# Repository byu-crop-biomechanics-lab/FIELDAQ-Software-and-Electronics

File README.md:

# FIELDAQ

## Running the Software on Raspberry PI 
1. Download the SD card [image](https://byu.box.com/s/8bjvmoukdaxu5hu80yromtlmhrw2ap65). You need at least a 16 GB SD card. 
2. Flash the SD card with the new image using whatever flash software you are accustomed to. For mac users I'd recommend using Apple PI Baker. 
3. Once flashed the device will open automatically in the command line interface and will boot the program automatically. Don't forget to to go to the settings and click the "update with github", or do it manually through the command line. 
4. If you want to make edits to the software or system as a whole and want to have a GUI, you can run the startx command and it will switch over to the Linux GUI. 

## Running the Software on Linux System (Non-Raspberry PI)
Run the following commands in a bash terminal to download, build and run the projcet. This build script will build a python environment and download the necessary packages. It then will build the project and run it to verify that everything is working correctly. 
```
git clone git@github.com:byu-crop-biomechanics-lab/FIELDAQ-Software-and-Electronics.git
cd FIELDAQ-Software-and-Electronics/
source build_project
```

After installing python and the nessesary [libraries](https://github.com/byu-crop-biomechanics-lab/FIELDAQ-Software-and-Electronics/blob/master/libraries.txt), the software is run by navigating into the [Granusoft/src](https://github.com/pr1ce1227/REAPER/tree/main/Granusoft/src) directory and running the [main.py](https://github.com/byu-crop-biomechanics-lab/FIELDAQ-Software-and-Electronics/blob/master/Granusoft/src/main.py) file.

The [main.py](https://github.com/byu-crop-biomechanics-lab/FIELDAQ/blob/master/Granusoft/src/main.py) file imports the necessary kivy library elements, and builds the kivy app. The companion [main.kv](https://github.com/byu-crop-biomechanics-lab/FIELDAQ-Software-and-Electronics/blob/master/Granusoft/src/main.kv) file imports the widgets (GUI screen elements), created for the use across the GUI, and imports the views that will be displayed throughout the app. These views are each composed of a python file and kivy file. More detail can be found in [Documentation/Kivy Screen Management.docx](https://github.com/byu-crop-biomechanics-lab/FIELDAQ-Software-and-Electronics/blob/master/Documentation/Kivy%20Screen%20Management.docx).

## Overview and Resources
The software for the FIELDAQ is written in python, using the kivy library. Versioning is managed using git via GitHub. The layout and functionality are based on the old DARLING software. With the addition of a touchscreen, kivy was utilized over pygame.

- [Resources for Python](https://www.python.org/about/gettingstarted/)
- Resources for kivy can be found in [Documentation/Kivy Training Resources](https://github.com/byu-crop-biomechanics-lab/FIELDAQ-Software-and-Electronics/tree/master/Documentation/Kivy%20Training%20Resources.docx)
- [Resources for git](https://guides.github.com/introduction/git-handbook/)
  - [The old DARLING repository](https://github.com/byu-crop-biomechanics-lab/DARLING_Software.git)

## Documentation Directory
The Documentation directory contains many useful files, some of which have been mentioned previously. Documentation that has been found to be the most useful is listed here:
- [Setup Software for Non-RPi Computers.txt](https://github.com/byu-crop-biomechanics-lab/FIELDAQ-Software-and-Electronics/blob/master/Documentation/Setup%20Software%20for%20Non-RPi%20Computers.txt) -  Information on how to get the GUI running on a non-RaspberryPi computer for software development.
- [Software Update Procedure.md](https://github.com/byu-crop-biomechanics-lab/FIELDAQ-Software-and-Electronics/blob/master/Documentation/Software%20Update%20Procedure.md) - Information on how to utilize a USB drive or Github when updating the on-device software.
- [FIELDAQ_Software_Diagrams.pdf](https://github.com/byu-crop-biomechanics-lab/FIELDAQ-Software-and-Electronics/blob/master/Documentation/FIELDAQ_Software_Diagrams.pdf) - Information about the screen navigation for the GUI and how each screen is built using kivy elements/widgets (flowchart is outdated).
- [Example_Adding the Camera Module.docx](https://github.com/byu-crop-biomechanics-lab/FIELDAQ-Software-and-Electronics/blob/master/Documentation/Example_Adding%20the%20Camera%20Module.docx) - A reflection on how the camera screens were added.
- [Example_Adding a Boot Screen.docx](https://github.com/byu-crop-biomechanics-lab/FIELDAQ-Software-and-Electronics/blob/master/Documentation/Example_Adding%20a%20Boot%20Screen.docx) - A hypothetical situation where a boot screen is created to choose between the Camera test mode and the Stalk Push testing mode.

### Structural Information of the Code Base (how is it assembled)
- [Directory Tree.txt](https://github.com/byu-crop-biomechanics-lab/FIELDAQ-Software-and-Electronics/blob/master/Documentation/Directory%20Tree.txt) -  Overview of the directories in the repository. With information about the contents of each directory.
- [FIELDAQ_Software_Diagrams.pdf](https://github.com/byu-crop-biomechanics-lab/FIELDAQ-Software-and-Electronics/blob/master/Documentation/FIELDAQ_Software_Diagrams.pdf) - 	Information about the screen navigation for the GUI and how each screen is built using kivy elements/widgets (flowchart is outdated).
- [Software Flowchart and Logic.docx](https://github.com/byu-crop-biomechanics-lab/FIELDAQ-Software-and-Electronics/blob/master/Documentation/Software%20Flowchart%20and%20Logic.docx) - 	Supplementary to FIELDAQ_Software_Diagrams, this document contains more information about the purpose of each screen.
- [Software Documentation Outdated.pdf](https://github.com/byu-crop-biomechanics-lab/FIELDAQ-Software-and-Electronics/blob/master/Documentation/Software%20Documentation%20Outdated.pdf) - 	An old resource containing the Classes and Methods contained in every file. This was last updated at the end of capstone, and may contain some useful information still. An updated version can be compiled using [DoxyGen](https://www.doxygen.nl/index.html) (version. 1.8.15).
### Background Information (how do the pieces work)
- [Kivy Screen Management.docx](https://github.com/byu-crop-biomechanics-lab/FIELDAQ-Software-and-Electronics/blob/master/Documentation/Kivy%20Screen%20Management.docx) - 	Information on how kivy navigates between screens and how screens can be added to the GUI.
- [Kivy Training Resources.docx](https://github.com/byu-crop-biomechanics-lab/FIELDAQ-Software-and-Electronics/blob/master/Documentation/Kivy%20Training%20Resources.docx) - 	A list of resources on how to learn kivy for those who are unfamiliar with the libraries.
- [Setup Software for Non-RPi Computers.txt](https://github.com/byu-crop-biomechanics-lab/FIELDAQ-Software-and-Electronics/blob/master/Documentation/Setup%20Software%20for%20Non-RPi%20Computers.txt) -  Information on how to get the GUI running on a non-RaspberryPi computer for software development.
- [Software Coding Standard.docx](https://github.com/byu-crop-biomechanics-lab/FIELDAQ-Software-and-Electronics/blob/master/Documentation/Software%20Coding%20Standard.docx) -	The Coding Standard for coding used throughout the software.
- [Software Update Procedure.md](https://github.com/byu-crop-biomechanics-lab/FIELDAQ-Software-and-Electronics/blob/master/Documentation/Software%20Update%20Procedure.md) - 	Information on how to utilize GitHub when updating the on-device software.
- Supplementary Directory:
  - [Kivy Clock Summary.docx](https://github.com/byu-crop-biomechanics-lab/FIELDAQ-Software-and-Electronics/blob/master/Documentation/Supplementary/Kivy%20Clock%20Summary.docx) - 	Information recorded by the capstone team about the logic for using the clock the way they did.
  - [Raspberry Pi Setup.docx](https://github.com/byu-crop-biomechanics-lab/FIELDAQ-Software-and-Electronics/blob/master/Documentation/Supplementary/Raspberry%20Pi%20Setup.docx) - 	Information on how to set up a new raspberry pi from scratch to host the software.
### Examples
- [Example_Adding the Camera Module.docx](https://github.com/byu-crop-biomechanics-lab/FIELDAQ-Software-and-Electronics/blob/master/Documentation/Example_Adding%20the%20Camera%20Module.docx) - A reflection on how the camera screens were added.
- [Example_Adding a Boot Screen.docx](https://github.com/byu-crop-biomechanics-lab/FIELDAQ-Software-and-Electronics/blob/master/Documentation/Example_Adding%20a%20Boot%20Screen.docx) - A hypothetical situation where a boot screen is created to choose between the Camera test mode and the Stalk Push testing mode.

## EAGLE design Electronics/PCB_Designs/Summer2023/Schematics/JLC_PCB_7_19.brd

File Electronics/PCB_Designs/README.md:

# PCB

The PCB_Designs sections gives current PCB files as well as files to help with the DRC, Gerber and BOM/CPL Files 
- Used www.jlcpcb.com for production

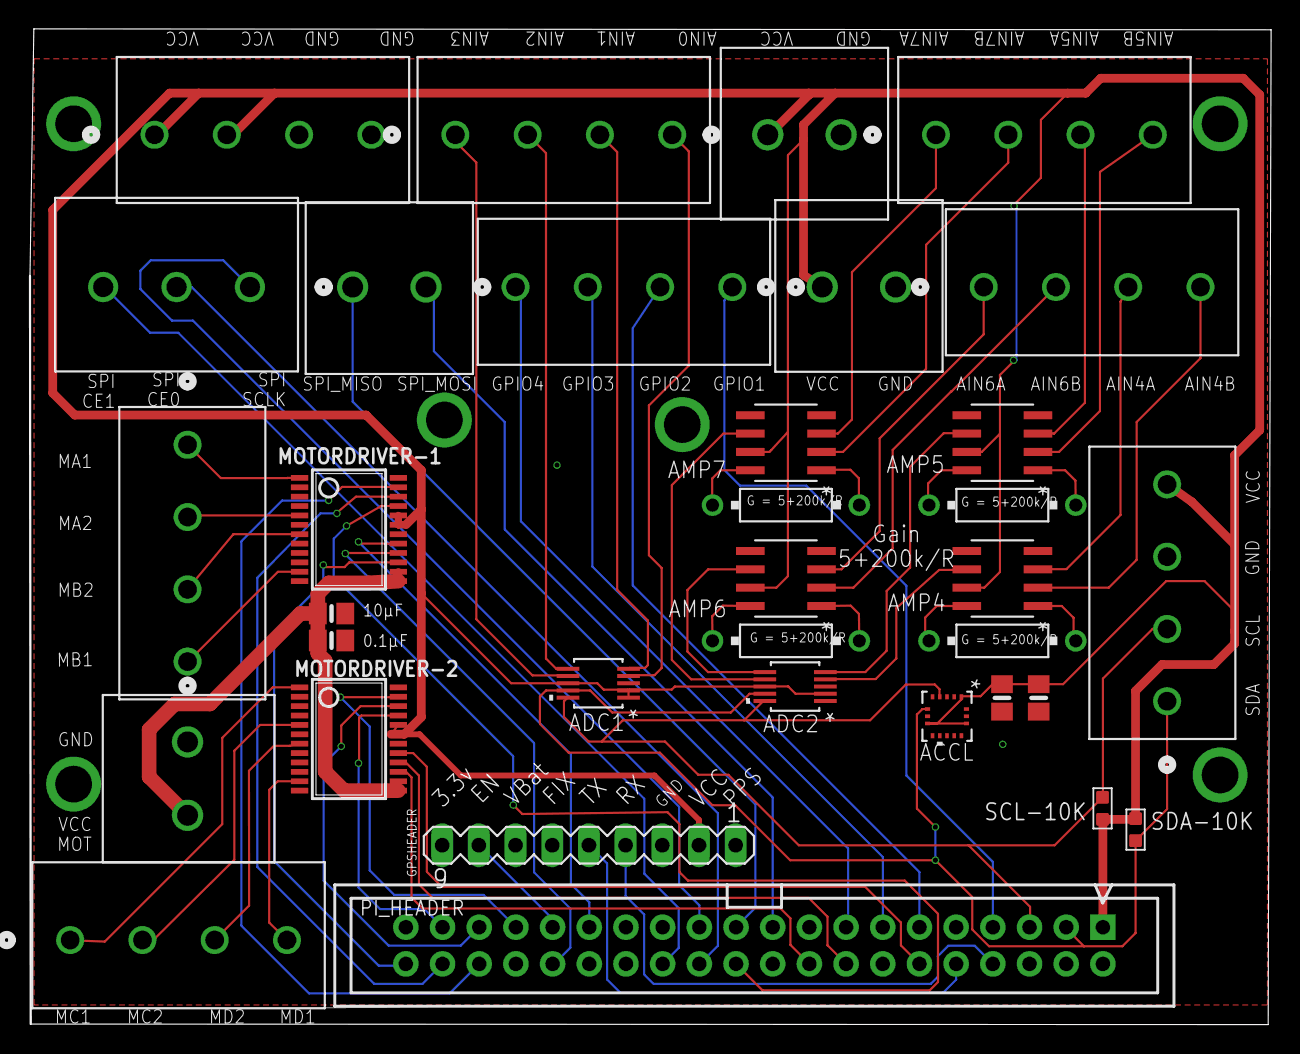
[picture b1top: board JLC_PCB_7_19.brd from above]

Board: 2 copper layers, 85.9 x 68.8 mm, 34 parts (0 on the bottom side), 61 nets.

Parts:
ACCL: LIS3DHTR; LGA-16_3X3X1MM
ADC1, ADC2: ADS1115IDGSR; DGS10
ADC2_AIN4_AMP, ADC2_AIN5_AMP, ADC2_AIN6_AMP, ADC2_AIN7_AMP: AD627ARZ-R7; R_8_ADI
ADC_1A_PWR, ADC_1A_SIG, ADC_2A_SIG, ADC_2B_SIG: 1715048; CONN_1715048_PXC
ADC_2A_PWR, ADC_2B_PWR: 1730612; CONN02_1730612_11P34X11P62_PXC
GPIO_A_: 1715048; CONN_1715048_PXC
GPIO_SPIA1: 1730612; CONN02_1730612_11P34X11P62_PXC
GPIO_SPIA2: 1730405; CONN_1730405_PXC
GPSHEADER: MA09-1
I2CA_: 1715048; CONN_1715048_PXC
MOTORDRIVER-1, MOTORDRIVER-2: TB6612 SSOP; SSOP24
MOTOR_1_A, MOTOR_2_: 1715048; CONN_1715048_PXC
MOTOR_1_B: 1730612; CONN02_1730612_11P34X11P62_PXC
PI_HEADER: RASPI_GPIO_B+#_BOX; RASPI_GPIO_B+_BOX
R5, R6, R7, R8: HPS58
SCL-10K: 10K 1/10W; R0603
SDA-10K: 10K 1/10W; R0603
VCC_10UF: 10µF; 0805-NO
VCC_.1UF: 0.1µF; 0805-NO
VMOTOR_10UF: 10µF; 0805-NO
VMOTOR_.1UF: 0.1µF; 0805-NO

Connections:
ADC1_AIN0: ADC1.4, ADC_1A_SIG.4
ADC1_AIN1: ADC1.5, ADC_1A_SIG.3
ADC1_AIN2: ADC1.6, ADC_1A_SIG.2
ADC1_AIN3: ADC1.7, ADC_1A_SIG.1
ADC2_AIN4: ADC2.4, ADC2_AIN4_AMP.6
ADC2_AIN4A: ADC2_AIN4_AMP.3, ADC_2B_SIG.3
ADC2_AIN4B: ADC2_AIN4_AMP.2, ADC_2B_SIG.4
ADC2_AIN5: ADC2.5, ADC2_AIN5_AMP.6
ADC2_AIN5A: ADC2_AIN5_AMP.3, ADC_2A_SIG.3
ADC2_AIN5B: ADC2_AIN5_AMP.2, ADC_2A_SIG.4
ADC2_AIN6: ADC2.6, ADC2_AIN6_AMP.6
ADC2_AIN6A: ADC2_AIN6_AMP.3, ADC_2B_SIG.1
ADC2_AIN6B: ADC2_AIN6_AMP.2, ADC_2B_SIG.2
ADC2_AIN7: ADC2.7, ADC2_AIN7_AMP.6
ADC2_AIN7A: ADC2_AIN7_AMP.3, ADC_2A_SIG.1
ADC2_AIN7B: ADC2_AIN7_AMP.2, ADC_2A_SIG.2
ADC_1: GPIO_SPIA1.1, PI_HEADER.19
AIN1: MOTORDRIVER-1.21, PI_HEADER.22
AIN2: MOTORDRIVER-1.22, PI_HEADER.38
BIN1: MOTORDRIVER-1.17, PI_HEADER.29
BIN2: MOTORDRIVER-1.16, PI_HEADER.32
CIN1: MOTORDRIVER-2.21, PI_HEADER.37
CIN2: MOTORDRIVER-2.22, PI_HEADER.35
DIN1: MOTORDRIVER-2.17, PI_HEADER.12
DIN2: MOTORDRIVER-2.16, PI_HEADER.16
EN: GPSHEADER.8, PI_HEADER.31
GND: ACCL.5, ACCL.7, ACCL.10, ACCL.12, ACCL.13, ACCL.15, ACCL.16, ADC1.3, ADC2.1, ADC2.3, ADC2_AIN4_AMP.4, ADC2_AIN4_AMP.5, ADC2_AIN5_AMP.4, ADC2_AIN5_AMP.5, ADC2_AIN6_AMP.4, ADC2_AIN6_AMP.5, ADC2_AIN7_AMP.4, ADC2_AIN7_AMP.5, ADC_1A_PWR.3, ADC_1A_PWR.4, ADC_2A_PWR.2, ADC_2B_PWR.2, GPSHEADER.3, I2CA_.3, MOTORDRIVER-1.3, MOTORDRIVER-1.4, MOTORDRIVER-1.9, MOTORDRIVER-1.10, MOTORDRIVER-1.18, MOTORDRIVER-2.3, MOTORDRIVER-2.4, MOTORDRIVER-2.9, MOTORDRIVER-2.10, MOTORDRIVER-2.18, MOTOR_1_B.1, PI_HEADER.6, PI_HEADER.9, PI_HEADER.14, PI_HEADER.20, PI_HEADER.25, PI_HEADER.30, PI_HEADER.34, PI_HEADER.39, VCC_10UF.2, VCC_.1UF.2, VMOTOR_10UF.2, VMOTOR_.1UF.2
GPIO1: GPIO_A_.1, PI_HEADER.7
GPIO2: GPIO_A_.2, PI_HEADER.11
GPIO3: GPIO_A_.3, PI_HEADER.13
GPIO4: GPIO_A_.4, PI_HEADER.15
MA1: MOTORDRIVER-1.1, MOTOR_1_A.1
MA2: MOTORDRIVER-1.5, MOTOR_1_A.2
MB1: MOTORDRIVER-1.11, MOTOR_1_A.4
MB2: MOTORDRIVER-1.7, MOTOR_1_A.3
MC1: MOTORDRIVER-2.1, MOTOR_2_.1
MC2: MOTORDRIVER-2.5, MOTOR_2_.2
MD1: MOTORDRIVER-2.11, MOTOR_2_.4
MD2: MOTORDRIVER-2.7, MOTOR_2_.3
unnamed: ADC2_AIN6_AMP.1, R5.1
unnamed: ADC2_AIN6_AMP.8, R5.2
unnamed: ADC2_AIN4_AMP.1, R7.1
unnamed: ADC2_AIN4_AMP.8, R7.2
unnamed: ADC2_AIN5_AMP.1, R8.1
unnamed: ADC2_AIN5_AMP.8, R8.2
unnamed: ADC2_AIN7_AMP.1, R6.1
unnamed: ADC2_AIN7_AMP.8, R6.2
PWMA: MOTORDRIVER-1.23, PI_HEADER.36
PWMB: MOTORDRIVER-1.15, PI_HEADER.40
PWMC: MOTORDRIVER-2.23, PI_HEADER.33
PWMD: MOTORDRIVER-2.15, PI_HEADER.18
RX: GPSHEADER.4, PI_HEADER.8
SCL: ACCL.4, ADC1.10, ADC2.10, I2CA_.2, PI_HEADER.5, SCL-10K.1
SDA: ACCL.6, ADC1.9, ADC2.9, I2CA_.1, PI_HEADER.3, SDA-10K.1
SPI_CE0: GPIO_SPIA2.2, PI_HEADER.24
SPI_CE1: GPIO_SPIA2.3, PI_HEADER.26
SPI_MISO: GPIO_SPIA1.2, PI_HEADER.21
SPI_SCLK: GPIO_SPIA2.1, PI_HEADER.23
TX: GPSHEADER.5, PI_HEADER.10
VCC: ACCL.1, ACCL.8, ACCL.14, ADC1.1, ADC1.2, ADC1.8, ADC2.2, ADC2.8, ADC2_AIN4_AMP.7, ADC2_AIN5_AMP.7, ADC2_AIN6_AMP.7, ADC2_AIN7_AMP.7, ADC_1A_PWR.1, ADC_1A_PWR.2, ADC_2A_PWR.1, ADC_2B_PWR.1, GPSHEADER.2, I2CA_.4, MOTORDRIVER-1.19, MOTORDRIVER-1.20, MOTORDRIVER-2.19, MOTORDRIVER-2.20, PI_HEADER.1, SCL-10K.2, SDA-10K.2, VCC_10UF.1, VCC_.1UF.1
VMOTOR: MOTORDRIVER-1.13, MOTORDRIVER-1.14, MOTORDRIVER-2.13, MOTORDRIVER-2.14, MOTOR_1_B.2, VMOTOR_10UF.1, VMOTOR_.1UF.1

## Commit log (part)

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2019-06-10 changed a file name to not have spaces
2019-06-10 Adjusted graphs on TestingResults and TestInProgress to automatically scale y axis to data in increments of 250.
2019-06-11 Adjusted y-scaling to improve calculation efficiency on device. Made graph backgrounds higher contrast.
2019-06-11 Re-added y-scaling after determining it is likely plotting all of the points on 2 graphs that could be causing time delays. Adjusted plot feature to plot only every 5th data point
2019-06-11 fixed .gitignore to ignore pycache files
2019-06-11 Added .gitignore file and deleted all pycaches.
2019-06-12 adjusted .gitignore file to address on device issues with .json files
2019-06-12 Adjusted config.json git settings to make configuration independant from software.
2019-06-12 adjusted how config was handled by git
2019-06-12 Adjusted Temperature sensor feed on main screen
2019-06-12 Fixed issue with trigger event for updating feed on the device
2019-06-13 Fixed update button
2019-06-13 Address error where no real data could cause a crash
2019-06-13 Added software update screen to move to when software update button is pressed.
2019-06-13 Adjusted testingresultsscreen
2019-06-13 Adding to previous commit, forgot to stage this change
2019-06-13 Adjusted how many digits are displayed on mainscreen and livefeedscreen. Adjusted layout of livefeedscreen to fit full coordinates.
2019-06-15 Undid unintentional change to elements.kv
2019-06-17 Added support to export location, temperature and humidity data in tests. Previously a pre-determined 40 value was given
2019-06-17 Fixed issue of mismatched parantheses
2019-06-18 Commented out select_all() command from Height, Operator, and Plot screens due to error caused by command. Will look into alternatives if feature is really necessary. The error was Error: Cant open d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
2019-06-19 Adjusted looks of Sensor Calibration Screens
2019-06-20 Added Screens for interface with Corn Stalkers device. Includes basic navigational functionality.
2019-06-21 Fixed Camera display. Next step is to change size of preview size.
2019-06-21 Added image capture capability.
2019-06-21 Adjusted filename of images and added Images folder to directory
2019-06-24 Adding a few jpgs to repository so that Images Directory is available to all.
2019-06-24 Adjusted naming scheme of ImageReviewScreen and added location data to image outputs.
2019-06-24 Added more metadata info to images.
2019-06-25 Adjusted layout and features of ImageReviewScreen.kv and ImagesViewScreen.kv
2019-06-25 Added delete image functionality
2019-06-25 Added Height, Plot, and Operator options to Camera Settings Screen.
2019-06-26 Added try catch to TestingResultsScreen about updating gps before saving the test.
2019-06-28 Adjusted how notes are written to saved tests to eliminate the creation of empty notes saved.
2019-07-18 Undid commit 37581237ce6649d85e913f2e0cc603e1e6c85f07 to restore a 1db35743d688aeaa57ebcfc2d5ad439a83008a01-like commit
2019-07-18 Fixed issue on device with 'uart' commands when changing the baud rate. Adjusted GPS refresh rate to 2 Hz in order to cycle through attempts faster when clearing the GPS flash memory. There is a dela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
2019-07-22 Fixed issue of X-Load results being multiples of 2. Adjusted so results now roughly map from 0 to 25 lbs similar to how the load scale is rated for. The ADC value is used for computations rather than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
2019-07-23 Added functionality to switch between ADC and converted values on LiveFeed Screen. All references to X Load and Potentiometer angle default to the converted values.
2019-07-23 Added clear_gps_memory command to CameraFeedScreen on pre-enter.
2019-07-23 Re-added the Images directory.
2019-07-24 Fixed issue with operator data in JSON not being a string when freshly installed or config.json file was deleted.
2019-07-24 Changed ADC View on LiveFeedScreen to display 0 decimals for ADC values and 3 decimals for converted units. This only affects x-load and potentiometer angle.
2019-07-26 Added file functionality to ImagesViewScreen. Ability to export and remove all images at once
2019-07-29 Exporting data now creates a folder with the date/time of the export and saves the config.json file as txt.
2019-07-31 Added Popup for when the USB is not detected and "Save to USB" is selected. Also adjusted logic for mounting/unmounting to test if USB is mounted or not.
2019-09-16 Fixed issue with going back from Archive screen
2019-09-18 Adjusted archivescreen to rid bootup CLI of warnings by renaming classes
2019-11-16 Fixing no temp/humidity sensor connection issue.
2020-03-17 Mount USB when export images is selected
2020-03-17 Fixed Image exporting empty files. USB can be plugged in and have images exported to them.
2020-05-26 added shutdown functionality on exit screen
2020-07-01 Adjusted unmounting sequence so that users accustomed to removing usb after use will not recieve only empty files. Note that the process seems to take much longer now to save files and unmount disk.
2020-07-31 Add side button that prints message when pressed. Proof of concept for identifying calibration points to delete.
2020-07-31 Reformat for loop to be in new function in CalibrateScreen class.
2020-07-31 Prints selected items only now. Time to remove the items from the json now.
2020-07-31 Ensure new python functionality is working.
2020-07-31 Added recalculation of intercept and slope as well as commented out all print messages.
2020-08-04 Archive CalibratePointScreen as CalibratePointsScreen
2020-08-04 Framework to pull one value in for ADC value when button is pressed. Multiple sampling needed soon.
2020-08-04 Removed reference CalibratePointsScreen*
2020-08-04 Prep dev branch for update and merging sensorCal into dev
2020-08-04 Added Restart button to Sensors Setting Screen to reload configuration data. Added message to inform user to restart device.
2020-08-07 Change destination of Save and Reject Test buttons on testingresults screen. Now navigates back to tests screen.
2020-08-10 Created TestDetailScreen to show plots of saved tests. Screen has no functionality or outside references. It is a copy of Testing_Results_Screen
2020-08-10 Selected test file information is passed to TestDetailScreen. Now displays filename of test as title on testDetailScreen.
2020-08-11 A graph is created. More fluff methods from copy and pasting testDetailScreen are removed. Next is to remove second plot and format view.
2020-08-11 Change testsscreen list to a test list of the singleselectablelist variety
2020-08-11 fix imu reference. realized fake data doesn't pull from the calibration files, so fixed reliance on that.
2021-05-04 Adding Documentation and comments. Software Diagrams contains info about screen navigation and elements available to use on the screen. Comments are added for clarity on main.py/kv
2021-05-05 Renamed files to remove capstone artifact naming.
2021-05-05 Adjusting readme.txt information to be more insightful.
2021-05-05 Reformated readme.txt to .md
2021-05-05 Fixed README formatting.
2021-05-07 Wrote most of Adding the Camera Module.docx. Adjusted some text in Adding a Boot Screen. Adjusted comments in CameraFeedScreen and CameraMainScreen kivy files.
2021-05-07 Revised documenation after another meeting with Dr. Cook. A new text file was added containing instructions on how to run the software on a computer other than a RaspberryPi. Revisions made to Adding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
2021-06-24 Added link to current image file
2021-07-07 Commented out old debug line
2021-07-12 Updated version number. 2.2.0 adds post-test viewing screen.
2021-07-16 Added comments to ImageDeleteConfirmation
2021-07-16 Added test delete confirmation
2021-07-16 Fixed individual image delete button
2021-08-11 Changed notes screen to say back instead of save
2021-08-11 Removed height, plot, and operator from settings (use testing screen instead)
2021-08-11 Added newline to 'upated notes' text from last commit
2021-08-11 Updated software update procedure to include USB
2021-08-11 Uploaded qr code for USB update command
2021-08-11 Added post-test notes in testResults screen
2021-08-11 Fixed bug where selected post-test notes would not clear after test
2021-08-11 Updated version number to 2.3.0
2021-08-11 Replaced photo to reflect latest command
2021-08-18 Added test settings confirmation screen before testing menu
2021-08-18 Added USB update button
2021-08-19 Switched csv file to save in milliseconds
2021-08-19 Update settings name for barcode
2021-08-19 Added zero padding to test number
2021-08-19 Fixed small bug with IMU code
2021-08-27 Added list of most useful documentation
    This list is simply what I found to be the most useful and it open to modification by future developers.
2023-08-14 Updated to add in Eagle PCB helps such as DRC, CAM, and BOM/CPL generatior, Added in current PCB
2023-08-18 Update connections.py
    Adjusted what terminals are being used, pot and height on 0 and 1 and force x and y on 6 and 7 respectively
2023-10-24 Base screen for mode select built
2023-10-24 Mode select functioning, need to rebuild file structure
2023-10-26 working pubsub, and requirments.tt
2023-10-30 working pubsub classes
2023-10-30 File structure complete for ARM and Camera
2023-10-30 Mode select
    * Base screen for mode select built
    * Mode select functioning, need to rebuild file structure
    * started file structure
    * continued File structure
    * New src working on ARM
    * File structure complete for ARM and Camera
2023-10-31 Added dogbone and darling directory
2023-10-31 Updated repo to include dogbone and darling
2023-11-06 added singleton placeholder files
2023-11-06 added singleton file
2023-11-06 part way through settings screens
2023-11-07 Continued
2023-11-07 Updated imports
2023-11-07 Updated Rod
2023-11-07 Cleaned up namespacing
2023-11-10 added devices to Devices folder
2023-11-10 fixed repeated imports
2023-11-10 Fixed exit button
2023-11-10 deleted extra folders
2023-12-07 Fixed ArchiveFolder
2023-12-08 Fixed many of the file path issues
2023-12-12 Files seem to be working now
2023-12-12 Continue
2024-01-10 Rename folder funciton is working
2024-01-23 Rodney working, needs to have sensors added
2024-01-29 Fixed x_load path
2024-01-30 commit 1
2024-01-30 commit 5
2024-01-31 Fixed barcode
2024-01-31 working version with config file that saves and is not overwritten
2024-02-01 removed duplication
2024-02-01 added imports
2024-02-01 code stuff
2024-02-02 updated stuff
2024-02-05 working code almost, but it reads from the ADCS
2024-02-06 added whiskers file
2024-02-06 removed strain8 from sensors screen
2024-02-06 added placeholder constants for rodney calibration
2024-02-06 stuff
2024-02-09 Fixed adc get data
2024-02-09 Folder system (#11)
    * Fixed ArchiveFolder
    * note screen fix
    * Fixed many of the file path issues
    * Basic file structure working
    * Fixed archiving problem
    * Files seem to be working now
2024-02-12 Fixed Github update to restart program cleanly
2024-02-13 Fixed warning
2024-03-08 fixed file system
2024-03-12 Fixed folder generation
2024-03-18 edited details
2024-03-19 Whiskers print to live screen
2024-03-21 Live screen has rate
2024-03-28 changes...
2024-04-03 Replaced darling connections with original
2024-04-03 added comment to X_Load on DARLING code saying it's not working
2024-06-24 add SingletonClass.py for singleton creation
    provides a superclass to inherit singleton function from
2024-06-24 Make SensorReal a singleton
    additionally, provides access to kivy logger to record when init is called
2024-06-28 updated to include TestLog

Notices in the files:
parts and their libraries:
COPYRIGHT: Copyright (C) 2023 Ultra Librarian. All rights reserved.
